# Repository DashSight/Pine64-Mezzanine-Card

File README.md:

# Pine64 Mezzanine Card

This is a open source hardware mezzanine card/hat/expansion board for the [SOPINE A64](https://www.pine64.org/sopine/) Single Board Computer (SBC). The project is developed using the open source EDA tool [KiCAD](http://kicad-pcb.org/).

This card adds the following features to the Pine64 SBC:

* OBDII Connection to communicate with a car's onboard diagnostics
  * SAE J1850 PWM
  * SAE J1850 VPW
  * ISO 9141-2
  * ISO 14230 KWP2000
  * ISO 15765 CAN
* GPS receiver to obtain current location
  * Battery backup to reduce power up time
  * External powered antenna to increase accuracy
  * PPS to increase accuracy of clock
* Inertial Measurement Unit (IMU) to detect acceleration and body roll
  * Connected via SPI
* 3 x [Qwiic](https://www.sparkfun.com/qwiic) connectors to expose other devices via I2C
* Support for a [1 wire temperature sensor](https://www.sparkfun.com/products/11050)

The version 3.0 is baed on the [ELM327](https://www.elmelectronics.com/ic/elm327/), the [u-blox NEO-M9N](https://www.u-blox.com/en/product/neo-m9n-module) Integrate Circuits (ICs) and the [LSM9DS1 IMU](https://www.st.com/en/mems-and-sensors/lsm9ds1.html).

## Licence

The design is licenced under the CERN-OHL-W licence.

The exception to this is the 3rd party [SparkFun libraries](https://github.com/sparkfun/SparkFun-KiCad-Libraries) which are used for the Qwiic connectors in the schematic and PCB. These are released under the [Creative Commons Attribution 4.0 International license](https://creativecommons.org/licenses/by/4.0/).

## v3.0 Production Run

More [pictures of v3.0](https://github.com/DashSight/Pine64-Mezzanine-Card/blob/master/PCB-Fabrication/v3.0/Photos) are avaliable

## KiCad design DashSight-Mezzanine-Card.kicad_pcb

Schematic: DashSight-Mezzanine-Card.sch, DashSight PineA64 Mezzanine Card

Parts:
BT1: 6.8mm-Coin-Cell; BatteryHolder_Keystone_2998_1x6.8mm
C1: 47pF; C_0603_1608Metric
C2, C5, C15, C16, C17: 0.1uF; C_0402_1005Metric
C3, C4: 560pF; C_0603
C6, C7: 27pF; C_0603
C8: 0.1uF; C_0402
C9: 10nF (16V); C_0402_1005Metric
C10: 10uF; C_0603_1608Metric
C11: 10uF 10V; C_0805_2012Metric
C12: 2.2uF 50V; CP_Radial_D5.0mm_P2.50mm
C13: 0.1uF 50V; C_0402_1005Metric
C14: 1uF; C_0603
C18: 10uF; CP_Radial_D4.0mm_P1.50mm
D1, D2: 1N4148; D_SOD-123
D3: 1N5819; D_SMA
D4: 0.5A/40V/420mV; D_0603_1608Metric
IC2: ELM327; DIP-28_W7.62mm
J1: Pi2 Connector; PinSocket_2x20_P2.54mm_Vertical
J2: Euler Connector; PinSocket_2x17_P2.54mm_Vertical
J3: Conn_Coaxial; U.FL_Hirose_U.FL-R-SMT-1_Vertical
J4: OBD2-DB9_Male; DSUB-9_Male_Horizontal_P2.77x2.84mm_EdgePinOffset4.94mm_Hou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
J5: Conn_02x05_Odd_Even; PinSocket_2x05_P2.54mm_Vertical
J6: Safeboot; PinHeader_1x01_P1.00mm_Vertical
J7: Reset; PinHeader_1x01_P1.00mm_Vertical
J8, J9, J10: QWIIC_CONNECTORJS-1MM; qwiic_connector
J14: 1W-PC16; PinHeader_1x03_P1.27mm_Vertical
JP1: DCIn-JP; PinHeader_1x02_P2.54mm_Vertical
JP2: Vbat-JP; PinHeader_1x02_P2.54mm_Vertical
L1: 30Ohm/1.8A; L_0603_1608Metric
Q1, Q4, Q5, Q6, Q7: 2N3904; SOT-23
Q2, Q3: 2N3906; SOT-23
R1: 10; R_0805_2012Metric
R2, R4, R8, R13: 470; R_0603
R3, R7, R17, R20, R22: 4.7K; R_0603
R5, R6: 100; R_0603
R9, R18, R19, R21: 10K; R_0603
R10, R23: 22K; R_0603
R11, R14, R26: 47K; R_0603
R12: 10K; R_0603_1608Metric
R15, R24, R25: 2.2K; R_0603
R16: 1.8K; R_0603
R27: 33K; R_0603
R28: 1K; R_0603
R29, R30: 510; R_0603
R37, R38: 2.2K; R_0603_1608Metric
SW1, SW2: SW_Push; PinHeader_1x02_P2.54mm_Vertical
U1: MCP2561-E/P; DIP-8_W7.62mm
U2: LM317L_TO92; TO-92_Inline
U3: LM1085IT-5.0; TO-220-3_Vertical
U4: ADuM1201AR; SOIC-8_3.9x4.9mm_P1.27mm
U5: NEO-M9N; ublox_NEO
U6: LSM9DS1; LGA-24L_3x3.5mm_P0.43mm
Y1: 4.0MHz; Crystal_HC49-U_Vertical

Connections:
+5V: C2.1, IC2.1 (~MCLR), IC2.5 (Memory), IC2.6 (Baud_Rate), IC2.7 (LFmode), IC2.15 (IgnMon), IC2.20 (Vdd), J2.2, J2.4, JP1.2, R22.1, U1.3 (VDD), U4.1 (VDD1)
CAN_High: J4.3, R6.1, U1.7 (CANH)
CAN_Low: J4.5, R5.1, U1.6 (CANL)
CAN_RX: IC2.24 (CAN_Rx), U1.4 (RXD)
CAN_TX: IC2.23 (CAN_Tx), U1.1 (TXD)
ELM_Pin12: IC2.12 (ISO_In), R26.2, R27.1
ELM_Pin14: IC2.14 (J1850_Bus-), R7.2
GND: BT1.2 (-), C1.2, C2.2, C3.2, C4.2, C5.2, C6.2, C7.2, C8.2, C9.2, C10.2, C11.2, C12.2, C13.2, C14.2, C15.2, C16.2, C17.2, C18.2, IC2.8 (Vss), IC2.19 (Vss), J1.6, J1.9, J1.14, J1.20, J1.25, J1.30, J1.34, J1.39, J2.6, J2.9, J2.14, J2.20, J2.25, J2.34, J3.2 (Ext), J4.0 (PAD), J4.1, J4.2, J5.6, J5.9, J8.1, J9.1, J10.1, J14.1, Q1.2, Q4.2, Q5.2, Q6.2, Q7.2, R12.2, R16.2, R19.2, R23.2, R27.2, SW2.1, U1.2 (VSS), U3.1 (GND), U4.4 (GND1), U4.5 (GND2), U5.7, U5.10, U5.12, U5.13, U5.24, U6.14, U6.15, U6.16, U6.17, U6.18, U6.19, U6.20
I2C1_SCL: J1.5, J8.4, J9.4, J10.4, R37.2
I2C1_SDA: J1.3, J8.3, J9.3, J10.3, R38.2
ISO9141-2_K: J4.4, Q7.3, R26.1, R30.2
ISO9141-2_L: J4.8, Q6.3, R29.2
J1850_Bus+: D1.1 (K), J4.7, R10.1, R18.1, R21.2
J1850_Bus-: D2.1 (K), J4.6, Q1.3, R10.2
unnamed: BT1.1 (+), C14.1, R28.2, U5.22
unnamed: C1.1, L1.2, R1.1
unnamed: C3.1, R5.2
unnamed: C4.1, R6.2
unnamed: C6.1, IC2.9 (XT1), Y1.1
unnamed: C7.1, IC2.10 (XT2), Y1.2
unnamed: C8.1, IC2.2 (Vmeasure), R11.2, R12.1
unnamed: C9.1, U6.21
unnamed: C11.1, JP1.1, U3.2 (VO)
unnamed: C15.1, U6.24
unnamed: D1.2 (A), Q2.3
unnamed: D2.2 (A), Q3.1, R14.1
unnamed: D4.1 (K), R28.1
unnamed: IC2.3 (J1850_Volts), R15.1
unnamed: IC2.4 (J1850_Bus+), R20.1
unnamed: IC2.11 (VPW_In), R21.1, R23.1
unnamed: IC2.13 (PWM_In), Q5.3, R22.2
unnamed: IC2.17 (RS232_Tx), U4.3 (VIB)
unnamed: IC2.18 (RS232_Rx), U4.2 (VOA)
unnamed: IC2.21 (ISO_K), R25.1
unnamed: IC2.22 (ISO_L), R24.1
unnamed: J3.1 (In), L1.1, U5.11
unnamed: J6.1, U5.1
unnamed: J7.1, U5.8
unnamed: Q1.1, R7.1
unnamed: Q2.1, R9.2, R17.1
unnamed: Q2.2, R8.1, R9.1, U2.2 (VO)
unnamed: Q3.2, R14.2, R18.2
unnamed: Q3.3, Q5.1, R19.1
unnamed: Q4.1, R20.2
unnamed: Q4.3, R17.2
unnamed: Q6.1, R24.2
unnamed: Q7.1, R25.2
unnamed: R1.2, U5.9
unnamed: R2.1, U5.21
unnamed: R3.1, U1.8 (STBY)
unnamed: R4.1, U5.20
unnamed: R8.2, R13.1, U2.1 (ADJ)
unnamed: R13.2, R15.2, R16.1
PC4: J1.32, U6.7
PC11: J1.40, U6.10
PH5: J1.29, J14.2
PH6: J1.31, U6.11
PH7: J1.26, U6.8
PH9: J1.13, U5.3
PowerOn: J5.5, SW1.2
PwrCntrl: IC2.16 (PwrCtrl), R3.2
ResetSW: J5.4, SW2.2
SPI0_CLK: J1.23, U6.2
SPI0_MISO: J1.21, U6.5, U6.6
SPI0_MOSI: J1.19, U6.4
UART2_RX: J1.10, R4.2
UART2_TX: J1.8, R2.2
UART3_RX: J2.23, U4.6 (VOB)
UART3_TX: J2.24, U4.7 (VIA)
V12: C10.1, C12.1, C13.1, D3.1 (K), U2.3 (VI), U3.3 (VI)
Vbat: D3.2 (A), JP2.2, R11.1, R29.1, R30.1
Vbat-OBD: J4.9, JP2.1

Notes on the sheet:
OBD2 DB9 Male Breakout
CAN Tx/Rx Logic
J1850 Bus Logic
ISO9141 Logic
Car 12V Input
V12 to V5
u-Blox GNSS Module and Antenna
Power On Button
Reset Button
50 Ohm Microstrip 0.2mm wide Copper Weight: 1oz/ft^2 Layer Thickness: 0.11mm Substrate: FR4 TG130 (4.29)
ELM327 OBDII
Inertial Measurement Unit (IMU)
I2C Expansion Qwiic Connectors
1-Wire GPIO Connections

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
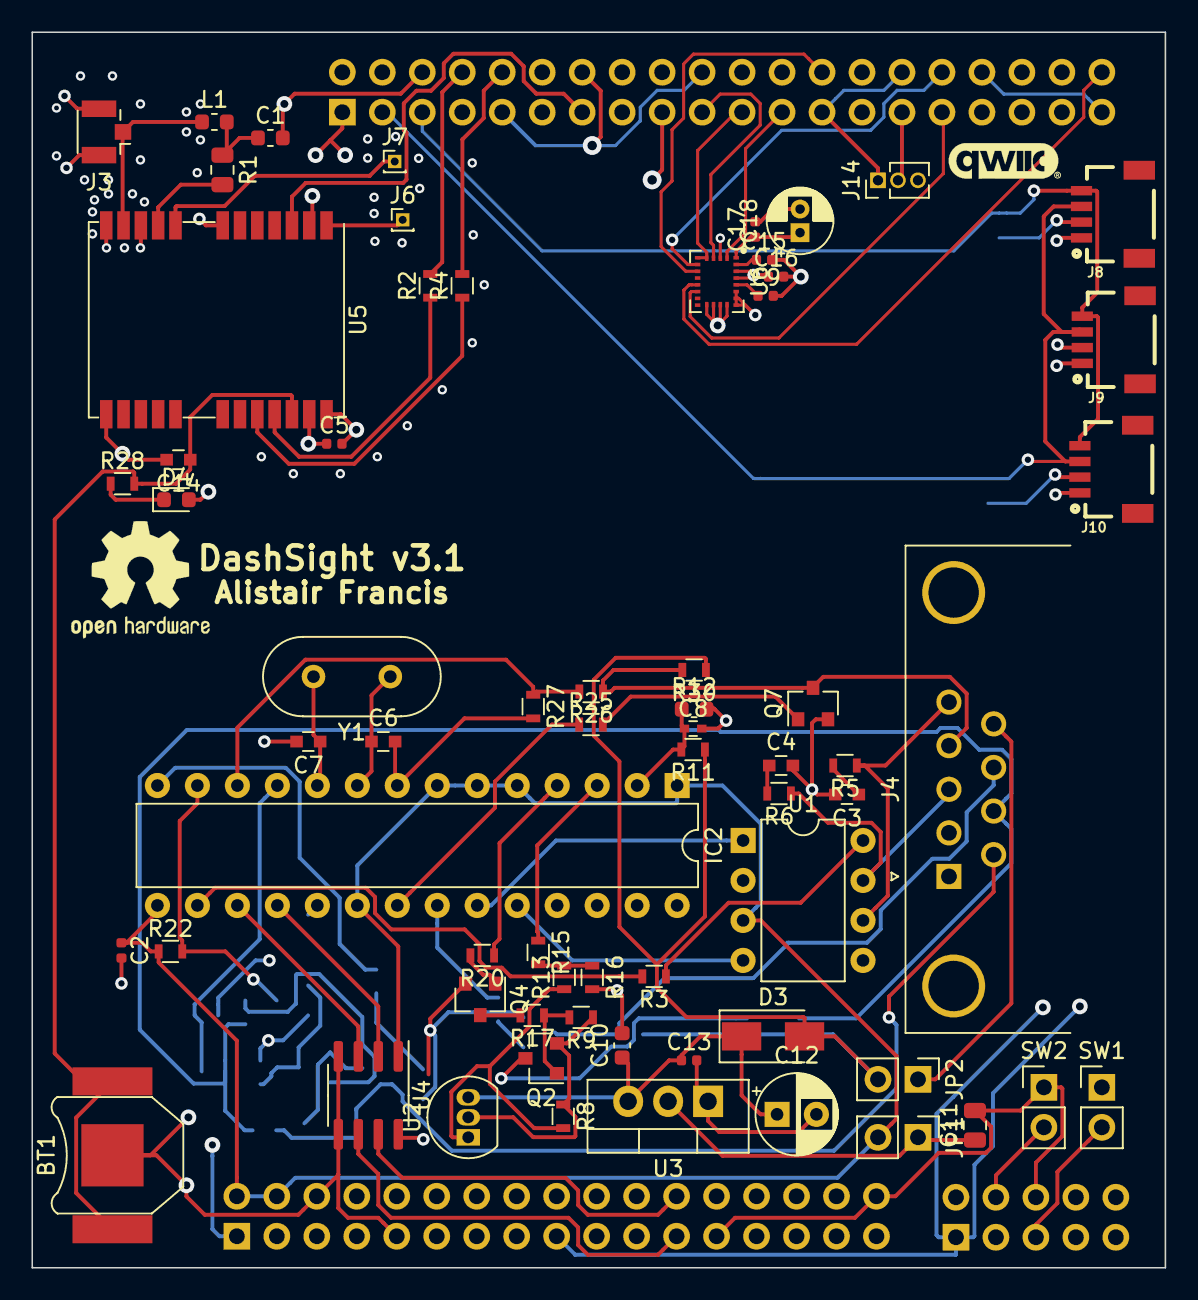
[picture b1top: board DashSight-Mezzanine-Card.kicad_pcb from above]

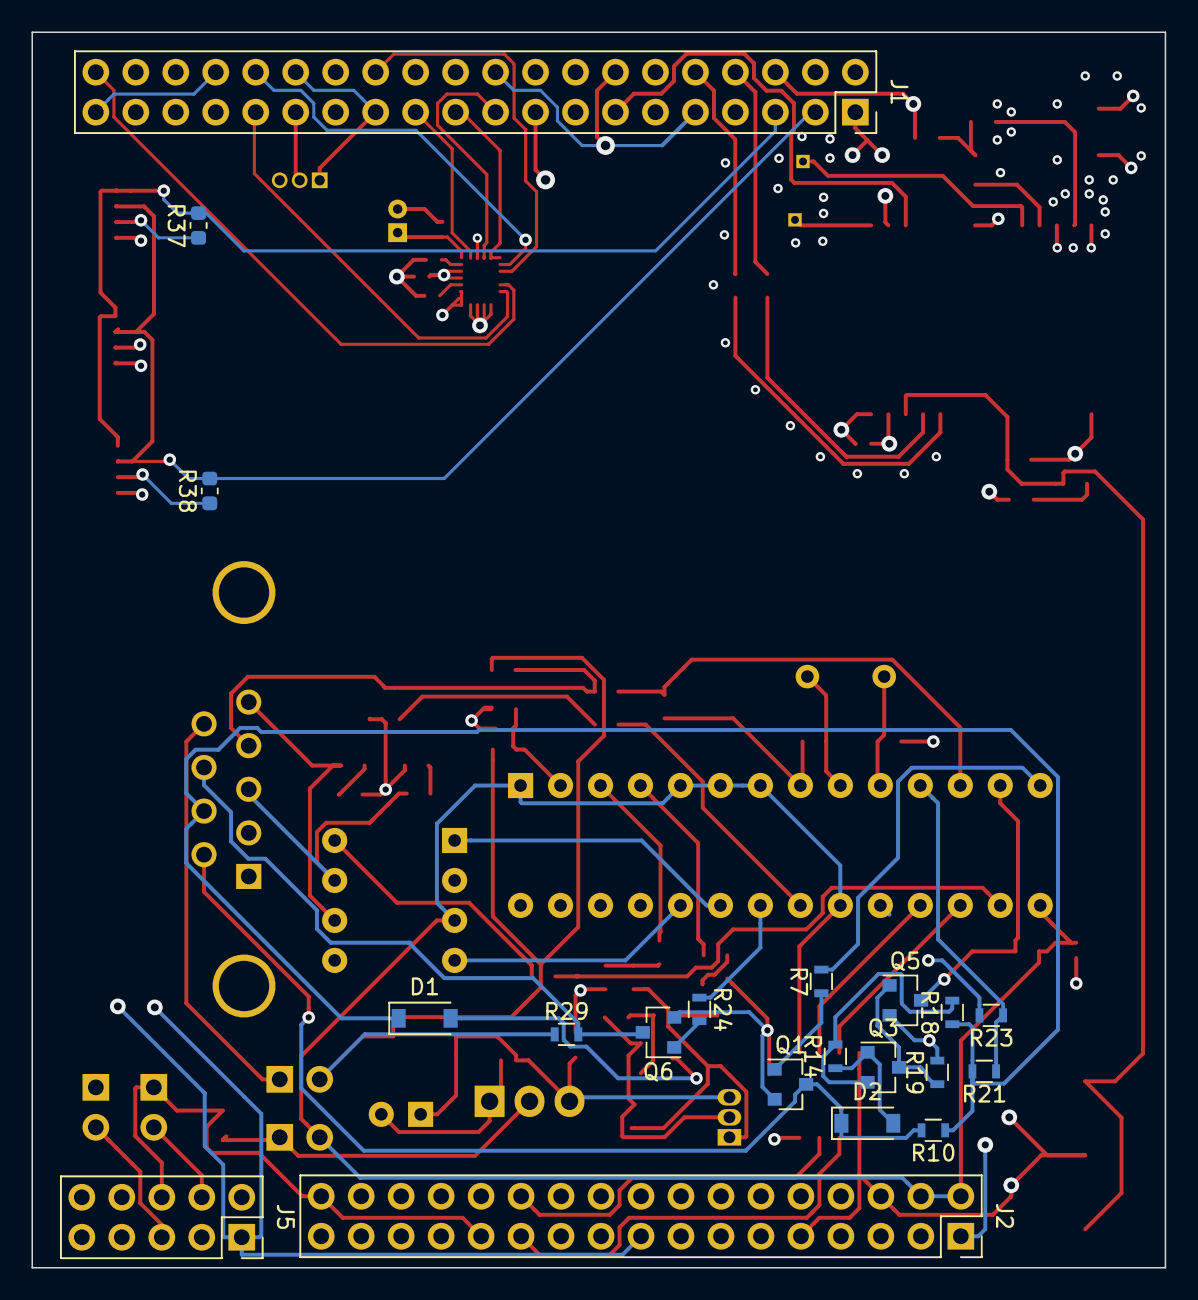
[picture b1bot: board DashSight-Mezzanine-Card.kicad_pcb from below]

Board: 4 copper layers, 72.0 x 78.5 mm, 86 parts (20 on the bottom side), 73 nets.

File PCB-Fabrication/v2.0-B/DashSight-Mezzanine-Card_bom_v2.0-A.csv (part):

"Source:","C:\Users\alist\OneDrive\Documents\DashSight\DashSight-Mezzanine-Card\DashSight-Mezzanine-Card.sch"
"Date:","25/07/2019 8:45:19 PM"
"Tool:","Eeschema (5.1.2)-1"
"Generator:","C:\Program Files\KiCad\bin\scripting\plugins/bom_csv_grouped_by_value.py"
"Component Count:","69"

"Individual Components:"

"Item","Qty","Reference(s)","Value","LibPart","Footprint","Datasheet"
"","","BT1","6.8mm-Coin-Cell","Device:Battery_Cell","DashSight-PCB-Footprints:BatteryHolder_Keystone_2998_1x6.8mm","2998"
"","","C1","1uF","Device:CP1","Capacitors_SMD:C_0603","CC0603ZRY5V7BB105"
"","","C2","0.1uF","Device:CP1","Capacitors_SMD:C_0402","CC0402KRX7R7BB104"
"","","C3","560pF","Device:CP1","Capacitors_SMD:C_0603","C0603C561K5RACTU"
"","","C4","560pF","Device:CP1","Capacitors_SMD:C_0603","C0603C561K5RACTU"
"","","C5","0.1uF","Device:CP1","Capacitors_SMD:C_0402","CC0402KRX7R7BB104"
"","","C6","27pF","Device:CP1_Small","Capacitors_SMD:C_0603","CC0603JRNPO9BN270"
"","","C7","27pF","Device:CP1_Small","Capacitors_SMD:C_0603","CC0603JRNPO9BN270"
"","","C8","0.1uF","Device:CP1","Capacitors_SMD:C_0402","CC0402KRX7R7BB104"
"","","C9","1uF","Device:CP1","Capacitors_SMD:C_0603","CC0603ZRY5V7BB105"
"","","C10","10uF 10V","Device:CP1","Capacitor_SMD:C_0805_2012Metric"," TAJR106M010RNJ "
"","","C11","10uF","Device:CP1","Capacitor_SMD:C_0603_1608Metric","CL10A106MQ8NNNC"
"","","C14","1uF","Device:CP1","Capacitors_SMD:C_0603","CC0603ZRY5V7BB105"
"","","D1","1N4148","Device:D","Diodes_SMD:D_SOD-123","1N4148W-TP"
"","","D2","1N4148","Device:D","Diodes_SMD:D_SOD-123","1N4148W-TP"
"","","D3","1N5819","Device:D","Diodes_SMD:D_SMA","1N5819"
"","","D4","0.5A/40V/420mV","Device:D_Schottky","Resistors_SMD:R_0402","VSKY05401006-G4-08"
"","","FB1","600Ohm/100MHz","Device:Ferrite_Bead","Inductors_SMD:L_0402","74279279"
"","","IC1","XM1110","SierraWireless-AirPrime:XM1110","RF_GPS:Sierra_XM11X0","XM1110_1103886"
"","","IC2","ELM327","elm327:ELM327","Housings_DIP:DIP-28_W7.62mm","ED281DT"
"","","J1","Pi2 Connector","Connector_Generic:Conn_02x20_Odd_Even","Pin_Headers:Pin_Header_Straight_2x20_Pitch2.54mm","PPPC202LFBN-RC"
"","","J2","Euler Connector","Connector_Generic:Conn_02x17_Odd_Even","Pin_Headers:Pin_Header_Straight_2x17_Pitch2.54mm","PPPC172LFBN-RC"
"","","J3","Conn_Coaxial","Connector:Conn_Coaxial","Connectors:SMA_THT_Jack_Straight","CONSMA002-G"
"","","J4","OBD2-DB9_Male","Connector:DB9_Male_MountingHoles","DashSight-PCB-Footprints:OBD2-Connector","A-DS 09 A/KG-T2S"
"","","JP1","DCIn-JP","Device:Jumper","Pin_Headers:Pin_Header_Straight_1x02_Pitch2.54mm","61300211121"
"","","JP2","Vbat-JP","Device:Jumper","Pin_Headers:Pin_Header_Straight_1x02_Pitch2.54mm","61300211121"
"","","L1","33nH","pspice:INDUCTOR","Inductors_SMD:L_0603","MHQ1005P33NJT000 "
"","","Q1","2N3904","Transistor_BJT:2N3904","TO_SOT_Packages_THT:TO-92_Molded_Narrow","2N3904"
"","","Q2","2N3906","Transistor_BJT:2N3906","TO_SOT_Packages_THT:TO-92_Molded_Narrow","2N3906"
"","","Q3","2N3906","Transistor_BJT:2N3906","TO_SOT_Packages_THT:TO-92_Molded_Narrow","2N3906"
"","","Q4","2N3904","Transistor_BJT:2N3904","TO_SOT_Packages_THT:TO-92_Molded_Narrow","2N3904"
"","","Q5","2N3904","Transistor_BJT:2N3904","TO_SOT_Packages_THT:TO-92_Molded_Narrow","2N3904"
"","","Q6","2N3904","Transistor_BJT:2N3904","TO_SOT_Packages_THT:TO-92_Molded_Narrow","2N3904"
"","","Q7","2N3904","Transistor_BJT:2N3904","TO_SOT_Packages_THT:TO-92_Molded_Narrow","2N3904"
"","","R1","10K","Device:R_Small","Resistors_SMD:R_0603","RC0603FR-0710KL"
"","","R2","470","Device:R_Small","Resistors_SMD:R_0603","RC0603JR-07470RL"
"","","R3","4.7K","Device:R","Resistors_SMD:R_0603","RC0603FR-074K7L"
"","","R4","470","Device:R_Small","Resistors_SMD:R_0603","RC0603JR-07470RL"
"","","R5","100","Device:R","Resistors_SMD:R_0603","RC0603JR-07100RL"
"","","R6","100","Device:R","Resistors_SMD:R_0603","RC0603JR-07100RL"
"","","R7","4.7K","Device:R","Resistors_SMD:R_0603","RC0603FR-074K7L"
"","","R8","470","Device:R","Resistors_SMD:R_0603","RC0603JR-07470RL"
"","","R9","10K","Device:R","Resistors_SMD:R_0603","RC0603FR-0710KL"
"","","R10","22K","Device:R","Resistors_SMD:R_0603","RC0603FR-0722KL"
"","","R11","47K","Device:R","Resistors_SMD:R_0603","RC0603JR-0747KL"
"","","R12","10K","Device:R","Resistors_SMD:R_0603","RC0603FR-0710KL"
"","","R13","470","Device:R","Resistors_SMD:R_0603","RC0603JR-07470RL"
"","","R14","47K","Device:R","Resistors_SMD:R_0603","RC0603JR-0747KL"
"","","R15","2.2K","Device:R","Resistors_SMD:R_0603","RC0603JR-072K2L"
"","","R16","1.8K","Device:R","Resistors_SMD:R_0603","RC0603FR-071K8L"
"","","R17","4.7K","Device:R","Resistors_SMD:R_0603","RC0603FR-074K7L"
"","","R18","10K","Device:R","Resistors_SMD:R_0603","RC0603FR-0710KL"
"","","R19","10K","Device:R","Resistors_SMD:R_0603","RC0603FR-0710KL"
"","","R20","4.7K","Device:R","Resistors_SMD:R_0603","RC0603FR-074K7L"
"","","R21","10K","Device:R","Resistors_SMD:R_0603","RC0603FR-0710KL"
"","","R22","4.7K","Device:R","Resistors_SMD:R_0603","RC0603FR-074K7L"
"","","R23","22K","Device:R","Resistors_SMD:R_0603","RC0603FR-0722KL"
"","","R24","2.2K","Device:R","Resistors_SMD:R_0603","RC0603JR-072K2L"
"","","R25","2.2K","Device:R","Resistors_SMD:R_0603","RC0603JR-072K2L"
"","","R26","47K","Device:R","Resistors_SMD:R_0603","RC0603JR-0747KL"
"","","R27","33K","Device:R","Resistors_SMD:R_0603","CRCW060333K0FKEAC"
"","","R28","1K","Device:R_Small","Resistors_SMD:R_0603","RC0603FR-071KL"
"","","R29","510","Device:R","Resistors_SMD:R_0603","RC0603JR-07510RL"
"","","R30","510","Device:R","Resistors_SMD:R_0603","RC0603JR-07510RL"
"","","U1","MCP2561-E/P","Interface_CAN_LIN:MCP2561-E-P","Housings_DIP:DIP-8_W7.62mm","MCP2561-E/P"
"","","U2","LM317L_TO92","Regulator_Linear:LM317L_TO92","TO_SOT_Packages_THT:TO-92_Inline_Narrow_Oval","LM317LZX"
"","","U3","LM1085-5.0","Regulator_Linear:LM1085-5.0","Package_TO_SOT_THT:TO-220F-3_Vertical","LM1085IT-5.0/NOPB"
"","","U4","ADuM1201AR","Isolator:ADuM1201AR","Housings_SOIC:SOIC-8_3.9x4.9mm_Pitch1.27mm","ADuM1201AR"
"","","Y1","4.0MHz","Device:Crystal","Crystals:Crystal_HC49-U_Vertical","ECS-040-20-4X-DU "



"Collated Components:"

"Item","Qty","Reference(s)","Value","LibPart","Footprint","Datasheet"
"1","1","BT1","6.8mm-Coin-Cell","Device:Battery_Cell","DashSight-PCB-Footprints:BatteryHolder_Keystone_2998_1x6.8mm","2998"
"2","3","C1, C9, C14","1uF","Device:CP1","Capacitors_SMD:C_0603","CC0603ZRY5V7BB105"
"3","3","C2, C5, C8","0.1uF","Device:CP1","Capacitors_SMD:C_0402","CC0402KRX7R7BB104"
"4","2","C3, C4","560pF","Device:CP1","Capacitors_SMD:C_0603","C0603C561K5RACTU"
"5","2","C6, C7","27pF","Device:CP1_Small","Capacitors_SMD:C_0603","CC0603JRNPO9BN270"
"6","1","C10","10uF 10V","Device:CP1","Capacitor_SMD:C_0805_2012Metric"," TAJR106M010RNJ "
"7","1","C11","10uF","Device:CP1","Capacitor_SMD:C_0603_1608Metric","CL10A106MQ8NNNC"
"8","2","D1, D2","1N4148","Device:D","Diodes_SMD:D_SOD-123","1N4148W-TP"
"9","1","D3","1N5819","Device:D","Diodes_SMD:D_SMA","1N5819"
"10","1","D4","0.5A/40V/420mV","Device:D_Schottky","Resistors_SMD:R_0402","VSKY05401006-G4-08"
"11","1","FB1","600Ohm/100MHz","Device:Ferrite_Bead","Inductors_SMD:L_0402","74279279"
"12","1","IC1","XM1110","SierraWireless-AirPrime:XM1110","RF_GPS:Sierra_XM11X0","XM1110_1103886"
"13","1","IC2","ELM327","elm327:ELM327","Housings_DIP:DIP-28_W7.62mm","ED281DT"
"14","1","J1","Pi2 Connector","Connector_Generic:Conn_02x20_Odd_Even","Pin_Headers:Pin_Header_Straight_2x20_Pitch2.54mm","PPPC202LFBN-RC"
"15","1","J2","Euler Connector","Connector_Generic:Conn_02x17_Odd_Even","Pin_Headers:Pin_Header_Straight_2x17_Pitch2.54mm","PPPC172LFBN-RC"
"16","1","J3","Conn_Coaxial","Connector:Conn_Coaxial","Connectors:SMA_THT_Jack_Straight","CONSMA002-G"
"17","1","J4","OBD2-DB9_Male","Connector:DB9_Male_MountingHoles","DashSight-PCB-Footprints:OBD2-Connector","A-DS 09 A/KG-T2S"
"18","1","JP1","DCIn-JP","Device:Jumper","Pin_Headers:Pin_Header_Straight_1x02_Pitch2.54mm","61300211121"
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
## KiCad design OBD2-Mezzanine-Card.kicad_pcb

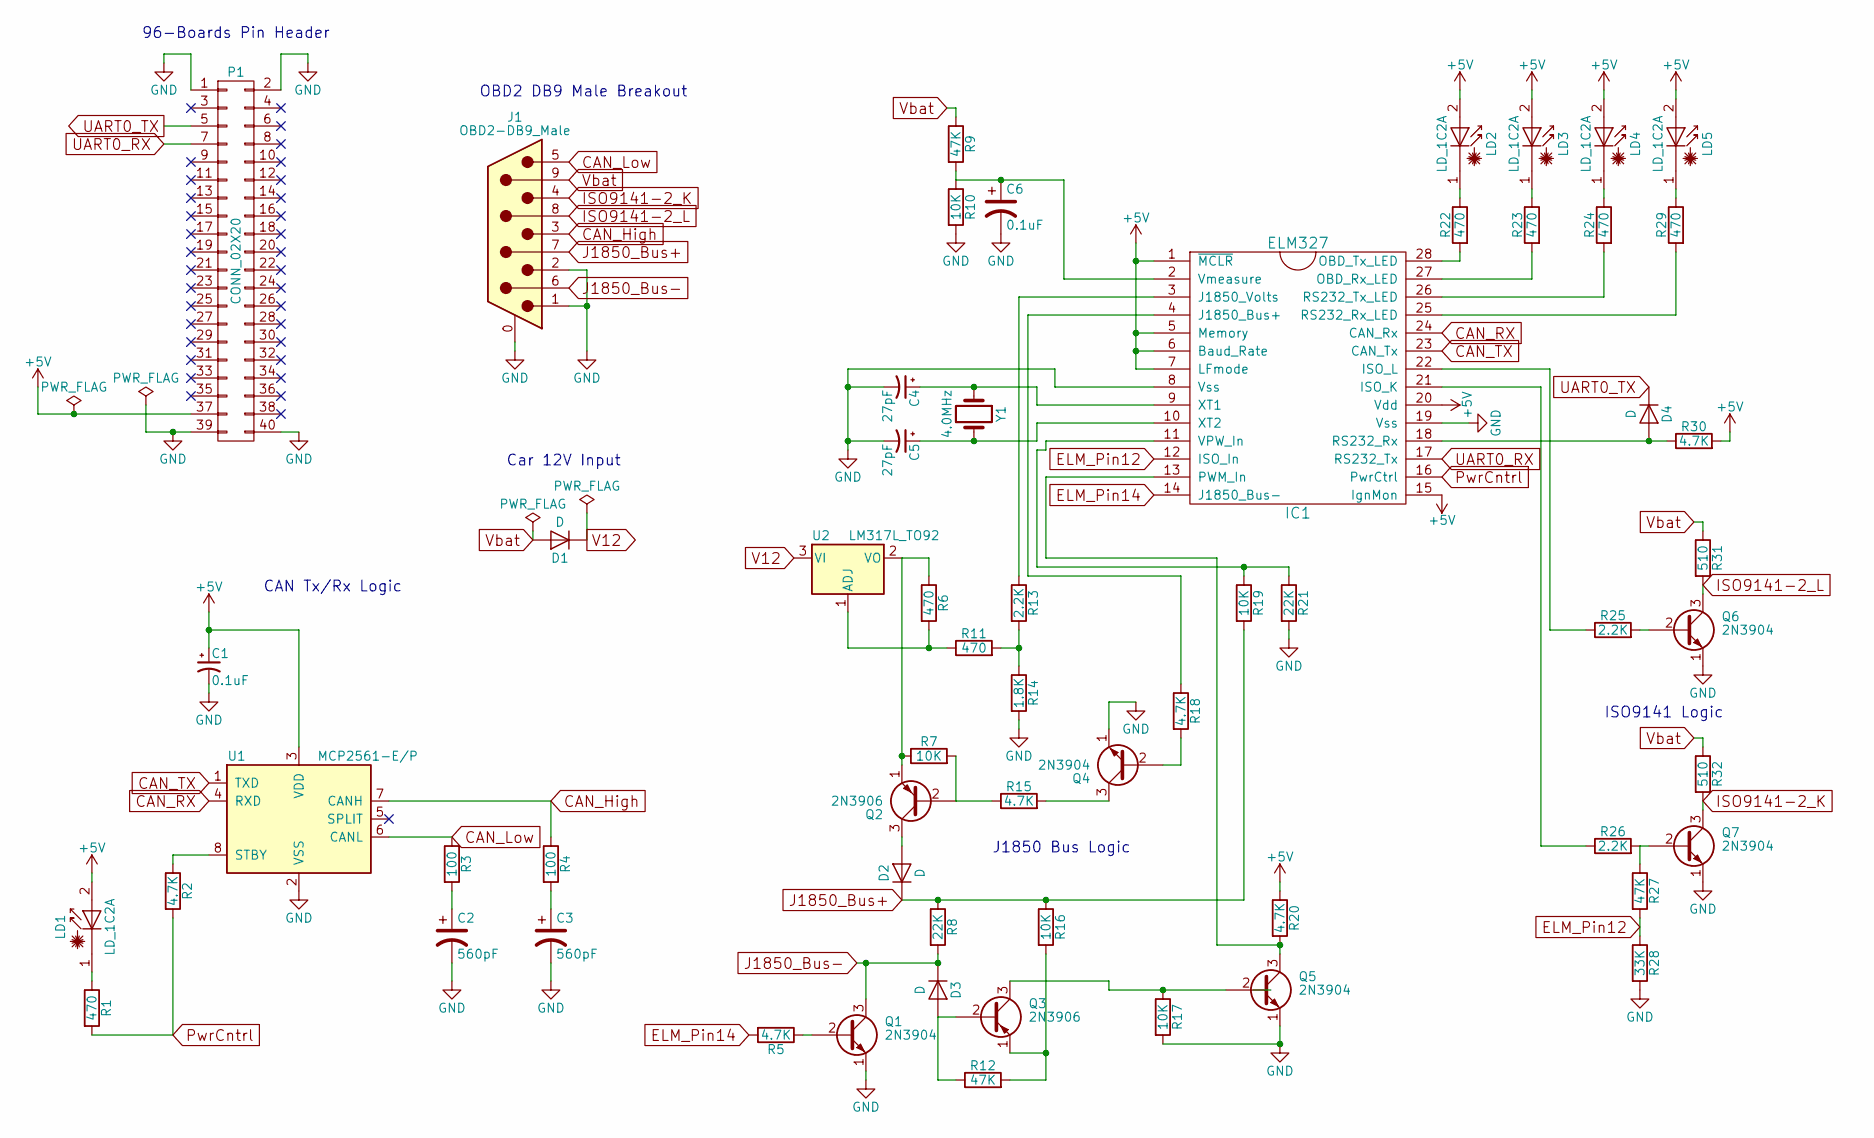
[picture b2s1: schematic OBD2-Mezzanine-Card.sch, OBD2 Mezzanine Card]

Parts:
C1, C6: 0.1uF; C_0603_HandSoldering
C2, C3: 560pF; C_0603_HandSoldering
C4, C5: 27pF; C_0603_HandSoldering
D1, D2, D3, D4: D; D_SOD-123
IC1: ELM327; DIP-28_W7.62mm
J1: OBD2-DB9_Male; DSUB-9_Male_Horizontal_Pitch2.77x2.84mm_EdgePinOffset4.94mm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
LD1, LD2, LD3, LD4, LD5: LD_1C2A; LaserDiode_TO3.3(D3.3)-3
P1: CONN_02X20; Pin_Header_Straight_2x20_Pitch2mm; Mfr Part # P220-1220A0xMxxxx2
Q1, Q4, Q5, Q6, Q7: 2N3904; TO-92_Molded_Narrow
Q2, Q3: 2N3906; TO-92_Molded_Narrow
R1, R6, R11, R22, R23, R24, R29: 470; R_0603_HandSoldering
R2, R5, R15, R18, R20, R30: 4.7K; R_0201
R3, R4: 100; R_0603_HandSoldering
R7, R10, R16, R17, R19: 10K; R_1206_HandSoldering
R8, R21: 22K; R_1206_HandSoldering
R9, R12, R27: 47K; R_1206_HandSoldering
R13, R25, R26: 2.2K; R_0201
R14: 1.8K; R_0201
R28: 33K; R_1206_HandSoldering
R31, R32: 510; R_0603_HandSoldering
U1: MCP2561-E/P; DIP-8_W7.62mm
U2: LM317L_TO92; TO-92_Inline_Narrow_Oval
Y1: 4.0MHz; Crystal_HC49-U_Vertical

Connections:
+5V: C1.1, IC1.1 (~MCLR), IC1.5 (Memory), IC1.6 (Baud_Rate), IC1.7 (LFmode), IC1.15 (IgnMon), IC1.20 (Vdd), LD1.2 (A), LD2.2 (A), LD3.2 (A), LD4.2 (A), LD5.2 (A), P1.37, R20.1, R30.2, U1.3 (VDD); also elsewhere on the board
CAN_High: J1.3, R4.1, U1.7 (CANH)
CAN_Low: J1.5, R3.1, U1.6 (CANL)
CAN_RX: IC1.24 (CAN_Rx), U1.4 (RXD)
CAN_TX: IC1.23 (CAN_Tx), U1.1 (TXD)
ELM_Pin12: IC1.12 (ISO_In), R27.2, R28.1
ELM_Pin14: IC1.14 (J1850_Bus-), R5.2
GND: C1.2, C2.2, C3.2, C4.2, C5.2, C6.2, IC1.8 (Vss), IC1.19 (Vss), J1.0 (PAD), J1.1, J1.2, P1.1, P1.2, P1.39, P1.40, Q1.1 (E), Q4.1 (E), Q5.1 (E), Q6.1 (E), Q7.1 (E), R10.2, R14.2, R17.2, R21.2, R28.2, U1.2 (VSS); also elsewhere on the board
ISO9141-2_K: J1.4, Q7.3 (C), R32.2
ISO9141-2_L: J1.8, Q6.3 (C), R31.2
J1850_Bus+: D2.1 (K), J1.7, R8.1, R16.1, R19.2
J1850_Bus-: D3.1 (K), J1.6, Q1.3 (C), R8.2
unnamed: C2.1, R3.2
unnamed: C3.1, R4.2
unnamed: C4.1, IC1.9 (XT1), Y1.1
unnamed: C5.1, IC1.10 (XT2), Y1.2
unnamed: C6.1, IC1.2 (Vmeasure), R9.2, R10.1
unnamed: D2.2 (A), Q2.3 (C)
unnamed: D3.2 (A), Q3.2 (B), R12.1
unnamed: D4.2 (A), IC1.18 (RS232_Rx), R30.1
unnamed: IC1.3 (J1850_Volts), R13.1
unnamed: IC1.4 (J1850_Bus+), R18.1
unnamed: IC1.11 (VPW_In), R19.1, R21.1
unnamed: IC1.13 (PWM_In), Q5.3 (C), R20.2
unnamed: IC1.21 (ISO_K), R26.1
unnamed: IC1.22 (ISO_L), R25.1
unnamed: IC1.25 (RS232_Rx_LED), R29.2
unnamed: IC1.26 (RS232_Tx_LED), R24.2
unnamed: IC1.27 (OBD_Rx_LED), R23.2
unnamed: IC1.28 (OBD_Tx_LED), R22.2
unnamed: LD1.1 (K), R1.1
unnamed: LD2.1 (K), R22.1
unnamed: LD3.1 (K), R23.1
unnamed: LD4.1 (K), R24.1
unnamed: LD5.1 (K), R29.1
unnamed: Q1.2 (B), R5.1
unnamed: Q2.1 (E), R6.1, R7.1, U2.2 (VO)
unnamed: Q2.2 (B), R7.2, R15.1
unnamed: Q3.1 (E), R12.2, R16.2
unnamed: Q3.3 (C), Q5.2 (B), R17.1
unnamed: Q4.2 (B), R18.2
unnamed: Q4.3 (C), R15.2
unnamed: Q6.2 (B), R25.2
unnamed: Q7.2 (B), R26.2, R27.1
unnamed: R2.1, U1.8 (STBY)
unnamed: R6.2, R11.1, U2.1 (ADJ)
unnamed: R11.2, R13.2, R14.1
PwrCntrl: IC1.16 (PwrCtrl), R1.2, R2.2
UART0_RX: IC1.17 (RS232_Tx), P1.7; also elsewhere on the board
UART0_TX: D4.1 (K), P1.5; also elsewhere on the board
V12: D1.1 (K), U2.3 (VI)
Vbat: D1.2 (A), J1.9, R9.1, R31.1, R32.1

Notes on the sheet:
96-Boards Pin Header
OBD2 DB9 Male Breakout
CAN Tx/Rx Logic
J1850 Bus Logic
ISO9141 Logic
Car 12V Input

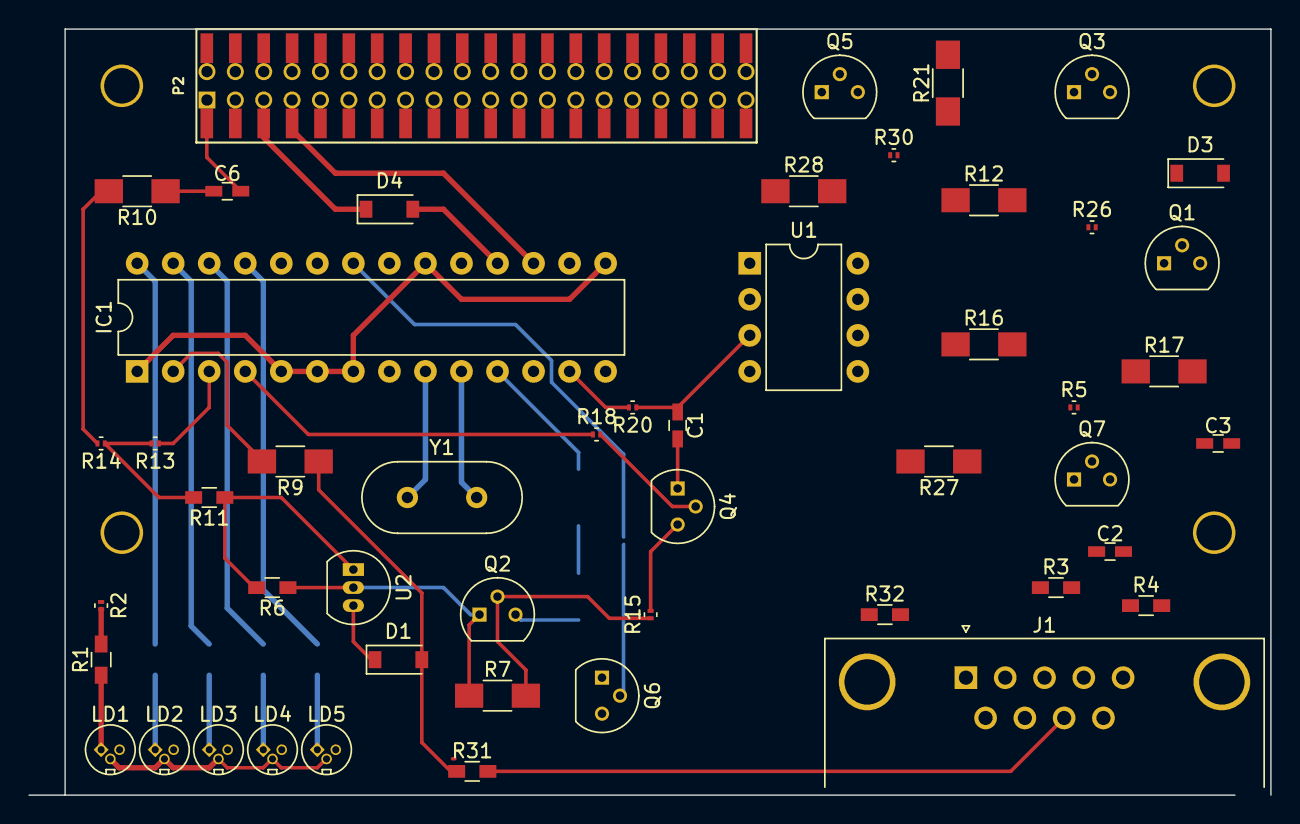
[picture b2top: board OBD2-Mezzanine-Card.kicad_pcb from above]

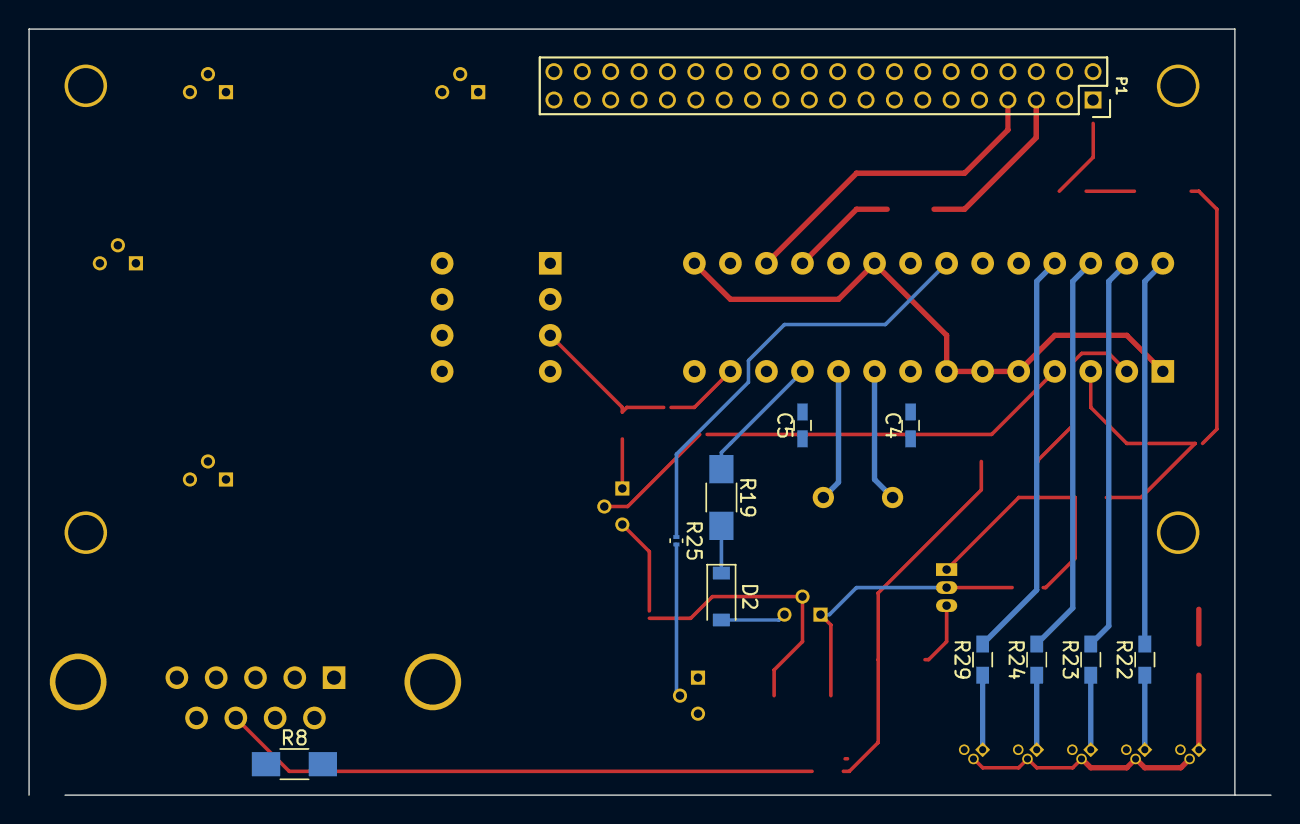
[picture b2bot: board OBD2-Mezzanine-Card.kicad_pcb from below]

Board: 2 copper layers, 87.5 x 54.0 mm, 61 parts (11 on the bottom side), 53 nets.

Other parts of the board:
P2: CONN_02X20; Socket_Strip_SMD_2x20_Pitch2mm

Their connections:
+5V: P2.37; also elsewhere on the board
GND: P2.1, P2.2, P2.39, P2.40; also elsewhere on the board
SYS_DCIN: P2.36, P2.38
UART0_RX: P2.7; also elsewhere on the board
UART0_TX: P2.5; also elsewhere on the board

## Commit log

2018-01-20 Initial Commit
    This is the initial commit based on the template avaliable here:
    https://github.com/96boards/96boards-kicad-mezzanine-template
2018-01-20 sch: Change to a through-hole non-stackable pin header
2018-01-20 sch: Delete Linaro notes
2018-01-21 Docs: Add the ELM327 and PIC docs
2018-03-12 lib: Add the ELM327 component
2018-03-12 sch: Update the title
2018-03-12 sch: Connect the Light Emitting Diodes
2018-03-12 sch: Connect some of the power options
2018-03-12 sch: Rearange
2018-03-12 sch: Add the MCP2561 CAN Transceiver
2018-03-12 sch: Start to connect the CAN transceiver
2018-03-12 Docs: Add some more datasheets
2018-03-12 sch: Add some more connections
2018-03-12 sch: Fixup a mistake
2018-03-15 sch: Add the OBD2 breakout
2018-03-15 sch: Connect the CAN High/Low to the ODB2
2018-03-15 sch: Connect Vmeassure
2018-03-15 sch: Initial commit of J1850 positivie bus
2018-03-15 sch: Rearange the schematic
2018-03-15 sch: Connect the J1850 Bus
2018-03-15 scho: Rearange a little bit
2018-03-15 Docs: Add the LM317L datasheet
2018-03-15 sch: Fix duplicate label
2018-03-15 sch: Connect the ISO9141-2 connections
2018-03-15 sch: Rearrange
2018-03-15 sch: Add the 12volt power supply
    Also rearrange a bit more
2018-03-15 Schematic.pdf: Initial commit
2018-03-15 sch: Add annotations
2018-03-15 lib: Update the ELM327 IC
2018-03-15 sch: Misc fixes to try to fix electrical checks
2018-03-15 Schematic.pdf: Update
2018-03-15 sch: Pass all electrical checks and add some lables
    Schematic is ready for review.
2018-03-15 Schematic.pdf: Update to review schematic
2018-03-20 sch: Add PCB footprints to most parts
2018-03-21 Connectors_DSub.pretty: Add the DSub connectors
2018-03-21 sch: Finalise the PCB footprints
2018-03-21 sch: Fix up the some PCB footprints
2018-03-21 kicad_pcd: Start to put the PCB together
2018-03-21 kicad_pcb: Start to connect tracks
2018-03-21 kicad_pcb: Continue to connect tracks
2018-03-21 kicad_pcb: Keep connecting
2018-05-16 kicad_pcb: Connect a large number of PCB devices
2018-11-17 DashSight: Convert from 96boards project to PineA64
2018-11-20 Docs: Add the GPS SoC
2018-11-20 sch: Update for the new Pine board
2018-11-21 Venus638FLPx.lib: Add the Venus library
2018-11-21 Update with the GPS IC
2018-11-21 More GPS connection updates
2018-11-22 Finalise schematics
2018-11-22 pcb: Add initial PCB
2018-11-22 sch: Small fix
2018-11-22 sch: Update PCB components
2018-11-22 Add the Venus638FLPx PCB footprint
2018-11-22 sch: Finish setting the PCB footprints
2018-11-22 sch: Fix wrong number of pins
2018-11-22 pcb: Add all the modules
2018-11-22 pcb: Kind of layout the board
2018-11-22 Show orientation of Venus IC and update PCB
2018-11-22 pcb: Continue improving layout
2018-11-22 pcb: Start to connect the tracks
2018-11-24 pcb: Continue connecting the traces
2018-11-25 DashSight-PCB-Footprints.pretty: Add a custom OBD2 PCB footprint
2018-11-25 pch: Finalise the PCB
2018-11-25 sch: Pick all parts
2018-11-25 Docs: Add more docs
2018-11-25 PCB-Fab: Add BOM
2018-11-25 PCB-Fab: Export required files
2018-11-25 sch: Fix capacitor BOM
2018-11-25 PCB-Fab: Increase board thickness
2018-11-25 PCB-Fab: Update to help prepare quotes
2018-11-28 BOM: Update to avaliable parts
2018-11-28 BOM: Update to use SeedStudio parts
2018-11-29 PCB-Fab: Update for SeedStudio Submission
2018-12-01 BOM: Change ELM IC to a IC socket instead
2018-12-01 Docs: Add some missing ones
2018-12-06 Connectors_DSub.pretty: Remove
2018-12-06 sch: Add a PDF of schematics
2019-02-17 Docs: Update the docs
2019-02-17 SierraWireless-AirPrime.lib: Add the AirPrime library
    Also remove the Venus one
2019-02-17 sch: Work on the v2.00 schematics
2019-02-17 sch: Rearange a little bit
2019-02-17 pdf: Remove old schematic
2019-02-21 Revert "pdf: Remove old schematic"
    This reverts commit 697014c673d4359312c34be824b0650e6c1d6efa, but moves
    the schematic into the PCB-Fabrication sub directory.
2019-02-21 sch: Update the J1850 bus diodes to match the ELM327 datasheet
2019-02-21 sch: Clarify the power input diode
2019-03-02 sch: Tidy up and review
2019-03-02 sch: Continue updating after review
2019-03-05 sch: Update some BOM parts
2019-03-05 PCB-Fab: Initial BOM commit
2019-03-05 sch: Add the XM1110 footprint
2019-03-05 lib: Rename XA1110 to XM1110
2019-03-05 sch: Update the BOM
2019-03-06 sch: Update R5
2019-03-06 docs: Add the battery holder specs
2019-03-06 sch: Project updates
2019-03-06 sch: Update footprint for U4
2019-03-06 sch: Change jumper footprints to straight
2019-03-06 sch: Fix connection errors
2019-03-06 pcb: Setup the PCB
2019-03-06 sch: Revert the annotation
2019-03-06 sch: Update with the new annotations
2019-03-06 Footprints: Add battery holder
2019-03-08 sch: Add battery holder footprint
2019-03-08 PCB-Fabrication: Update BOM
2019-03-08 kicad_pcb: Update based on the latest schematics
2019-03-08 kicad_pcb: Update the PCB
2019-03-11 sch: Update PCB thickness and track width for RF
2019-03-11 kicad_pcb: Connect the GPS RF
2019-03-11 kicad_pcb: Remove incorrect tracks
2019-03-16 kicad_pcb: Misc changes
2019-03-16 kicad_pcb: Update KiCAD version and close outline
2019-03-16 kicad_pcb: Connect remaining components
2019-03-16 kicad_pcb: Cleanup tracks and vias
2019-03-17 kicad_pcb: Finalise design
2019-03-17 PCB-Fab: Add v2.00A Schematic
2019-03-17 kicad_pcb: Move battery holder onto board
2019-03-17 sch: Change symbol from XA1110 to XM1110
2019-03-17 PCB-Fab: Update BOM
2019-03-17 PCB-Fab: Add v2.00A Fabrication Options
2019-03-17 PCB: Reduce antenna distance and regenerate production files
2019-03-17 PCB-Fab: Add some notes
2019-03-20 sch: Update date on schematic
2019-03-20 BOM: Update the BOM
2019-03-20 kicad_pcb: Add OSH logo and regenerate PCB-Fab
2019-05-14 sch: Fix the Antenna connector part
2019-06-26 PCB-Fab: Add some pictures of v2.0-A
2019-06-26 PCB-Fab: Improve version information
2019-06-26 README: Initial commit
2019-06-26 LICENSE: Initial commit
2019-06-29 LICENSE and README updates
2019-07-23 BatteryHolder_Keystone_2998: Update based on latest PR
2019-07-23 sym-lib-table: Remove old symbol libraries
2019-07-23 sch: Update to latest KiCAD release
2019-07-26 sch: Update the OBD2 voltage regulator
2019-07-26 pcb: Replace with the new voltage regulator
2019-07-26 Update with the official KiCAD XM1110
2019-07-26 Docs: Remove some less important documents
2019-07-26 project: Cleanup backup and working files
2019-07-26 Docs: Remove some more documents and add a new one
2019-07-26 .gitignore: Update to ignore fp-info-cache
2019-07-26 pcb: Add my name to the PCB
2019-07-26 PCB-Fab: Start to prepare the v2.0-B release
2019-07-26 PCB-Fab: Add the v2.0-B schematic
2019-07-26 sch: Update the version information
2019-07-26 PCB-Fab: Add v2.0-B output
2019-07-26 .gitignore: Ignore the cache-lib file
2019-12-08 .gitignore: Ignore the fp-lib-table file
2019-12-23 Footprints: Update based on update PR
2019-12-23 PCB-Fab: Update v2.0-B output
2019-12-23 PCB-Fab: Add the assembly files
2019-12-28 Docs: Add GNSS Hardware Design Reference
2020-01-06 Footprints: Update battery holder based on merged PR
2020-03-29 pcb: Update GPS layout
2020-03-29 sch: Remove custom OBD connector
2020-03-30 pcb: Consolidate PCB layout
2020-03-30 PCB-Fab: Remove v2.0-B releae files
2020-03-30 pcb: Shrink the board
2020-04-03 PCB-Fab: Add some more details
2020-04-08 Docs: Add some more GNSS docs
2020-04-08 Docs: Add the NEO-M9N documentation
2020-04-08 sch: Add u-Blox GNSS for v3.00
2020-04-09 sch: Fixup missing components
2020-04-09 sch: Finalise the GNSS design
2020-04-10 sch: Add a button to turn the board on
2020-04-10 sch: Add a reset button
2020-04-10 sch: Small fixups in the layout
2020-04-10 sch: Annotate schematic
2020-04-10 sch: Don't use through hold PNP/NPN parts
2020-04-10 sch: Add components for new headers
2020-04-11 sch: Pick some GNSS components
2020-04-11 sch: Pick all of the current parts
2020-04-11 pcb: Upgrade to 4 layers and start to prep GNSS
2020-04-11 pcb: Add ground and power planes on inner layers
2020-04-11 sch: Add a power decoupling cap for GNSS 3V3
2020-04-11 pcb: Start to connect up the GNSS receiver
2020-04-12 sch: Fix the reset button connection
2020-04-12 sch: Update all of the footprints
2020-04-12 pcb: Place and route the ELM327
2020-04-12 Remove the old Sierra Wireless Library
2020-04-12 sch: Fixup some errors
2020-04-12 Docs: Add another GNSS doc
2020-04-12 sch: Update the microstrip numbers
2020-04-25 sch: Connect the PPS from GNSS
2020-04-25 sch: Remove the Zener Diode from GNSS
2020-04-25 pcb: Connect the GNSS PPS
2020-04-25 sch: Add the LSM9DS1 IMU
2020-04-25 sch: Fixup resistor types
2020-04-25 sch: Improve the GNSS breakout headers
2020-04-26 footprints: Add a Qwiic logo
2020-04-27 Add the Qwiic connector PCB and Schematic files
2020-04-27 sch: Update the schematic to include Qwiic
2020-04-28 sch: Update the headers and power supply
2020-04-28 pro: Add a new track width
2020-04-28 pcb: Connect the IMU, GNSS PPS, Qwiic and other changes
2020-04-28 README: Update licence and the readme
2020-04-28 Breakout some GPIOs and fixup remaining issues
2020-04-28 pcb: Small corrections
2020-04-28 Only support 6 Qwiic connections
    I was worried I couuldn't fit the cables in with 6
2020-04-28 Shrink the Qwiic logo
2020-04-28 README: Fixup broken links
2020-04-29 sch: Update some of the footprints
2020-04-29 sch: Add a jumper to enable SPI for the IMU
2020-04-29 Revert "sch: Add a jumper to enable SPI for the IMU"
    This reverts commit a1cdc124bf6f11fea9068c468dfdf75d15ab77d8.
2020-04-29 pcb: Update some of the footprints
2020-04-30 Update based on BOM avaliability
2020-04-30 PCB-Fab: Generate fab files
2020-05-01 Revert "Revert "sch: Add a jumper to enable SPI for the IMU""
    This reverts commit c516a7607144a3527f6f3ebaa38245544a61c706.
2020-05-02 sch: Update all of the pin connections
2020-05-02 pcb: Update some of the trace spacing
2020-05-02 PCB-Fab: Update with latest submission
2020-05-02 pcb: Update based from the schematics
2020-05-03 PCB-Fab: Update the files for the v3.0 production
2020-05-03 Add photos of the v3.0 render
2020-05-19 sch: Update to the latest KiCAD release
2020-05-19 Docs: Remove outdated docs
2020-05-19 PCB-Fab: Add some position files used for v0.3
2020-09-12 sch: Fixup some of the component types
2020-09-12 kicad_pcb: Move headers closer together
2020-09-12 sch/pcb: Update the GPS connected to U.FL
    Also fixup some missing connections and bump PCB and schematic
    versions.
2020-10-14 sch: Fix the BJT Transistors
2020-10-15 sch: Upgrade the voltage regulator
2020-10-15 gitignore: Update to ignore more sch-bak
2020-10-15 Docs: Remove some old docs
2020-10-15 sch: Upgrade voltage regulator to LM1085
2020-11-05 sch: Use shorter headers
2020-12-29 sch: Fix the PPS GPIO to be interrupt capable
2020-12-29 kicad_pcb: Update the PCB based on the new schematic
2021-01-03 README: Update the README
2021-01-04 PCB-Fab: Add some new photos
2021-01-04 README: Use a better picture
